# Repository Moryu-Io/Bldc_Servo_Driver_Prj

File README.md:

# BLDC Servo Driver Project

## 概要
STM32マイコンを使用してBLDCを駆動する制御プログラム  
マイコン種類が変わっても、なるべくペリフェラル設定のメンテのみで動作が可能なように実装  
現在のメイン開発は`G431CB_FSDmini`

新ROBO-剣出場ロボット[Quinque](https://www.robo-one.com/rankings/view/1127)のアーム部モータに採用  

## フォルダ構成
| フォルダ名   | 説明                                                                                            |
| ------------ | ----------------------------------------------------------------------------------------------- |
|bldc_servo_driver_mini_F4|STM32F405を使用したBLDCドライバ用コード(未メンテ)|
|bldc_servo_driver_mini_G4|STM32G4系マイコンを使用したBLDCドライバ用コード|
|bldc_servo_driver_mini_H7|STM32H7を使用したBLDCドライバ用コード(未作成)|
|bldc_servo_driver_stspin32g4|STM32G4(STSPIN32G4)を使用したBLDCドライバ用コード|
|common|各マイコンで共通のコード。例えばBLDCベクトル制御ロジック|
|python|各テストコマンドをpython経由で使用するためのスクリプト群|

## 使い方(Windows)
1. 必要Toolのインストール
    - VScode
    - GNU ARM Embedded Toolchain
        - [公式サイト](https://developer.arm.com/tools-and-software/open-source-software/developer-tools/gnu-toolchain/gnu-rm/downloads)
        - Projectとしては2020-q4を使っている。本PJのtask.jsonに記載のディレクトリを変えれば別Verでも使えるはず
        - zip版をDLし, C:\Tools\gcc-arm-none-eabi-9-20XX-qX-major-win32\bin など分かりやすいように配置し、Path を通しておく
    - makeするための何か
        - make for windows, msys2, wslなど。自分は現状msys2でmakeを使えるようにしている
        - 本PJのtask.jsonでは`C:\\msys64\\usr\\bin\\make.exe` がある前提で記載している
    - STM32CubeProgrammer
        - [公式サイト]https://www.st.com/ja/development-tools/stm32cubeprog.html
        - STM32マイコンへのFW書き込みやフラッシュ制御などができる
        - 本PJのtask.jsonではコマンドライン用のexeを利用してマイコンへの書き込みを行っている

2. クローン
    - `git clone https://github.com/Moryu-Io/Bldc_Servo_Driver_Prj.git`など
    - VSCode のタスク構成もついてくるはず

3. VSCode Workspaceを開く
    - 現在は`bldc_servo_driver_G4.code-workspace`推奨

4. Ctrl+Alt+t でタスクを開き`Build project`を実行すると、ビルドができる

5. Ctrl+Alt+t でタスクを開き`cube_program`を実行すると書き込みができる

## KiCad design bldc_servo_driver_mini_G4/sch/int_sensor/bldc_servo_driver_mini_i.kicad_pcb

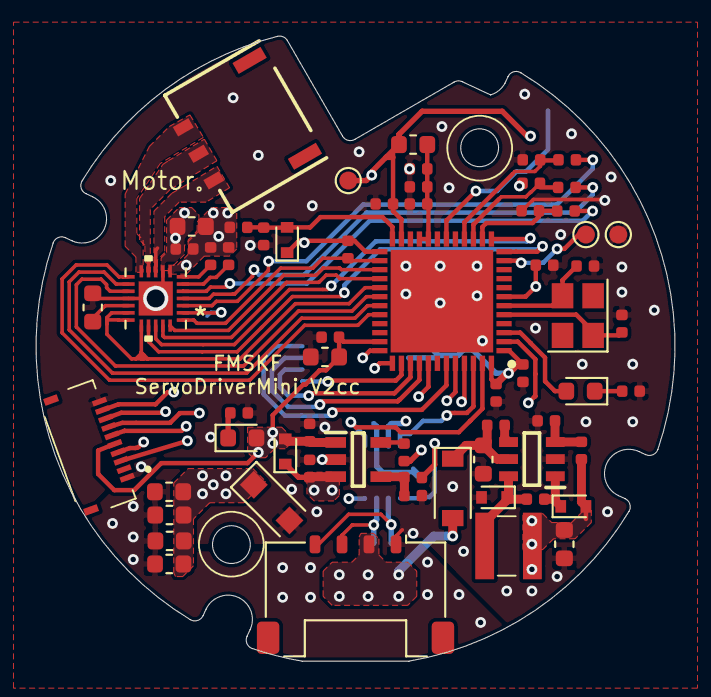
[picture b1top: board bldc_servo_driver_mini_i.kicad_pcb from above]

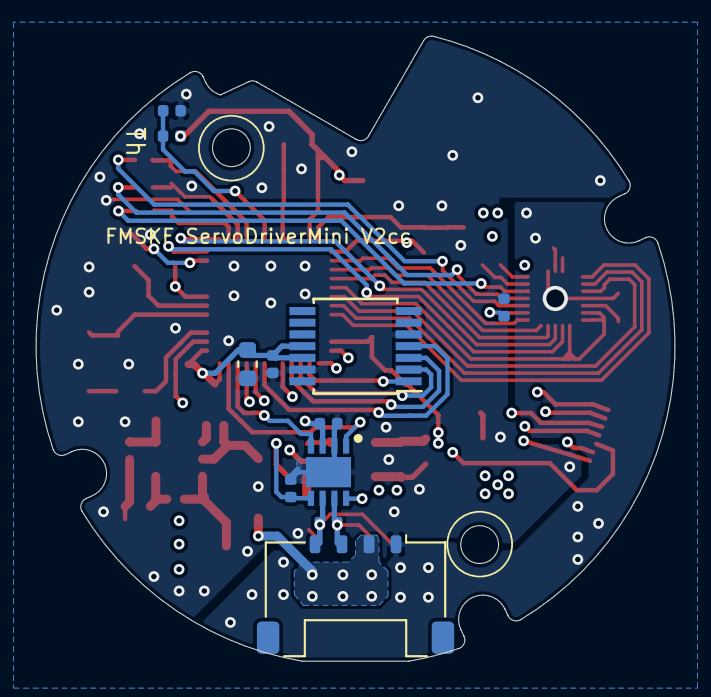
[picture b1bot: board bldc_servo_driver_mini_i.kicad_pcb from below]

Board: 4 copper layers, 35.5 x 34.7 mm, 74 parts (11 on the bottom side), 56 nets.

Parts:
C1, C2, C3, C4, C7, C8, C10, C16, C20, C21, C24, C32: 0.1u; C_0402_1005Metric
C5, C11, C15, C22, C28, C29, C30, C31: 10u; C_0603_1608Metric
C6, C13: 0.01u; C_0402_1005Metric
C9, C14, C23: 1u; C_0402_1005Metric
C12, C25: 4.7u; C_0603_1608Metric
C17, C18, C19: 220pF; C_0402_1005Metric
C26, C27: 8p; C_0402_1005Metric
D1: D_Schottky; D_SOD-123F
D2: PMEG6010AESBYL; D_SOD-123
D3, D4, D9: D_Schottky; D_SOD-523
D5: BAT30KFILM; D_SOD-523
D6, D8: LED; LED_0603_1608Metric
IC1: ST730MR; SOT95P280X145-5N
IC2: LT1616ES6#TRMPBF; SOT95P280X90-6N
IC3: TLT9251VLEXUMA1; SON65P300X300X110-9N
IC4: STM32G4xxyU; QFN50P700X700X60-49N-D
J1: 1-2328702-0; 123287020
J2, J3: Conn_01x04; Molex_Pico-Lock_504050-0491_1x04-1MP_P1.50mm_Horizontal
J7: DF65-3P-1.7V_21_
L1: L; L_0603_1608Metric
L2: 4.7u; LPS3314332MRC
R3, R4, R16, R18, R20: 10k; R_0402_1005Metric
R5: 47k; R_0402_1005Metric
R6: 27k; R_0402_1005Metric
R7: 470k; R_0402_1005Metric
R8: 33k; R_0402_1005Metric
R9, R10, R11: 510; R_0402_1005Metric
R12, R14: 330; R_0402_1005Metric
R15: 60; R_0402_1005Metric
R17: 0; R_0402_1005Metric
R19: 30.1k or 51k(MP2359); R_0402_1005Metric
TH1: Thermistor_NTC; R_0402_1005Metric
TP1, TP2, TP3: TestPoint; TestPoint_Pad_D1.0mm
U1: AS5048A; TSSOP-14_4.4x5mm_P0.65mm
U2: PDRV8311HRRWR
Y1: Crystal; Crystal_SMD_Abracon_ABM8G-4Pin_3.2x2.5mm

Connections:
+3V3: C1.1, C2.1, C5.2, C7.2, C9.1, C10.1, C12.1, C20.1, C21.1, C32.2, D3.2, D5.1, D8.2, IC1.1, IC3.5, IC4.1, IC4.23, IC4.25, IC4.35, IC4.48, J1.5, L1.2, R5.2, R16.1, R18.2, TP1.1, U1.11, U1.12, U2.2
+5V: C8.1, C16.1, C29.2, D3.1, D9.2, IC1.3, IC3.3, L2.2, R4.1, R19.2
+12V: C11.2, C22.1, C23.1, C24.1, C28.2, C30.2, C31.2, D1.1, D2.2, J2.2, J3.2, R7.2, R17.1, U2.8
/CAN1_EN: IC3.8, IC4.2
/CAN1_RX: IC3.4, IC4.46
/CAN1_TX: IC3.1, IC4.47
/CAN_H: IC3.7, J2.3, J3.3, R15.2
/CAN_L: IC3.6, J2.4, J3.4, R15.1
/CurrentSensA: C17.1, IC4.14, R9.1
/CurrentSensB: C18.1, IC4.15, R10.1
/CurrentSensC: C19.1, IC4.16, R11.1
/DAC_O1_GAIN: IC4.12, U2.21
/DAC_O2_SLEW: IC4.13, U2.22
/GPIO_MODE: IC4.28, U2.23
/LED1: D6.2, IC4.3
/M_OUTA: J7.1, U2.10
/M_OUTB: J7.2, U2.11
/M_OUTC: J7.3, U2.12
/NRST: C3.1, IC4.7, J1.4
/Potentio_Sens: IC4.11, TP2.1
/SOA: R9.2, U2.5
/SOB: R10.2, U2.4
/SOC: R11.2, U2.3
/SPI3_CS: IC4.38, U1.1
/SPI3_MISO: IC4.40, U1.3
/SPI3_MOSI: IC4.43, U1.4
/SPI3_SCK: IC4.39, U1.2
/SWCLK: IC4.37, J1.7
/SWDIO: IC4.36, J1.6
/SWO: IC4.41, J1.3
/TIM1_CH1: IC4.30, U2.15
/TIM1_CH1N: IC4.29, U2.18, U2.19, U2.20
/TIM1_CH2: IC4.31, U2.14
/TIM1_CH3: IC4.32, U2.13
/Temp_Sens: IC4.18, R18.1, TH1.1
/USART1_RX: IC4.45, J1.9
/USART1_TX: IC4.44, J1.8
/Vm_Sens: D5.2, IC4.24, R7.1, R8.2
/nFAULT: IC4.26, R16.2, U2.1
/nSLEEP: IC4.27, U2.24
GND: C1.2, C2.2, C3.2, C4.2, C5.1, C7.1, C8.2, C9.2, C10.2, C11.1, C12.2, C13.2, C14.2, C15.1, C16.2, C17.2, C18.2, C19.2, C20.2, C21.2, C22.2, C24.2, C25.1, C26.1, C27.2, C28.1, C29.1, C30.1, C31.1, C32.1, D1.2, D4.2, IC1.2, IC2.2, IC3.2, IC3.9, IC4.49, J1.1, J1.10, J2.1, J3.1, R6.1, R8.1, R12.1, R14.1, R20.1, TH1.2, TP3.1, U1.5, U1.13, U2.9, U2.16, U2.25
unnamed: C6.1, D9.1, IC2.1
unnamed: C6.2, D4.1, IC2.6, L2.1
unnamed: C4.1, C13.1, C14.1, IC4.20, IC4.21, L1.1
unnamed: C15.2, D2.1, IC2.5, R3.2
unnamed: C23.2, U2.6
unnamed: C25.2, U2.17
unnamed: C26.2, IC4.5, Y1.1
unnamed: C27.1, IC4.6, Y1.3
unnamed: D6.1, R12.2
unnamed: D8.1, R14.2
unnamed: IC1.4, R5.1, R6.2
unnamed: IC1.5, R4.2
unnamed: IC2.3, R19.1, R20.2
unnamed: IC2.4, R3.1
unnamed: R17.2, U2.7

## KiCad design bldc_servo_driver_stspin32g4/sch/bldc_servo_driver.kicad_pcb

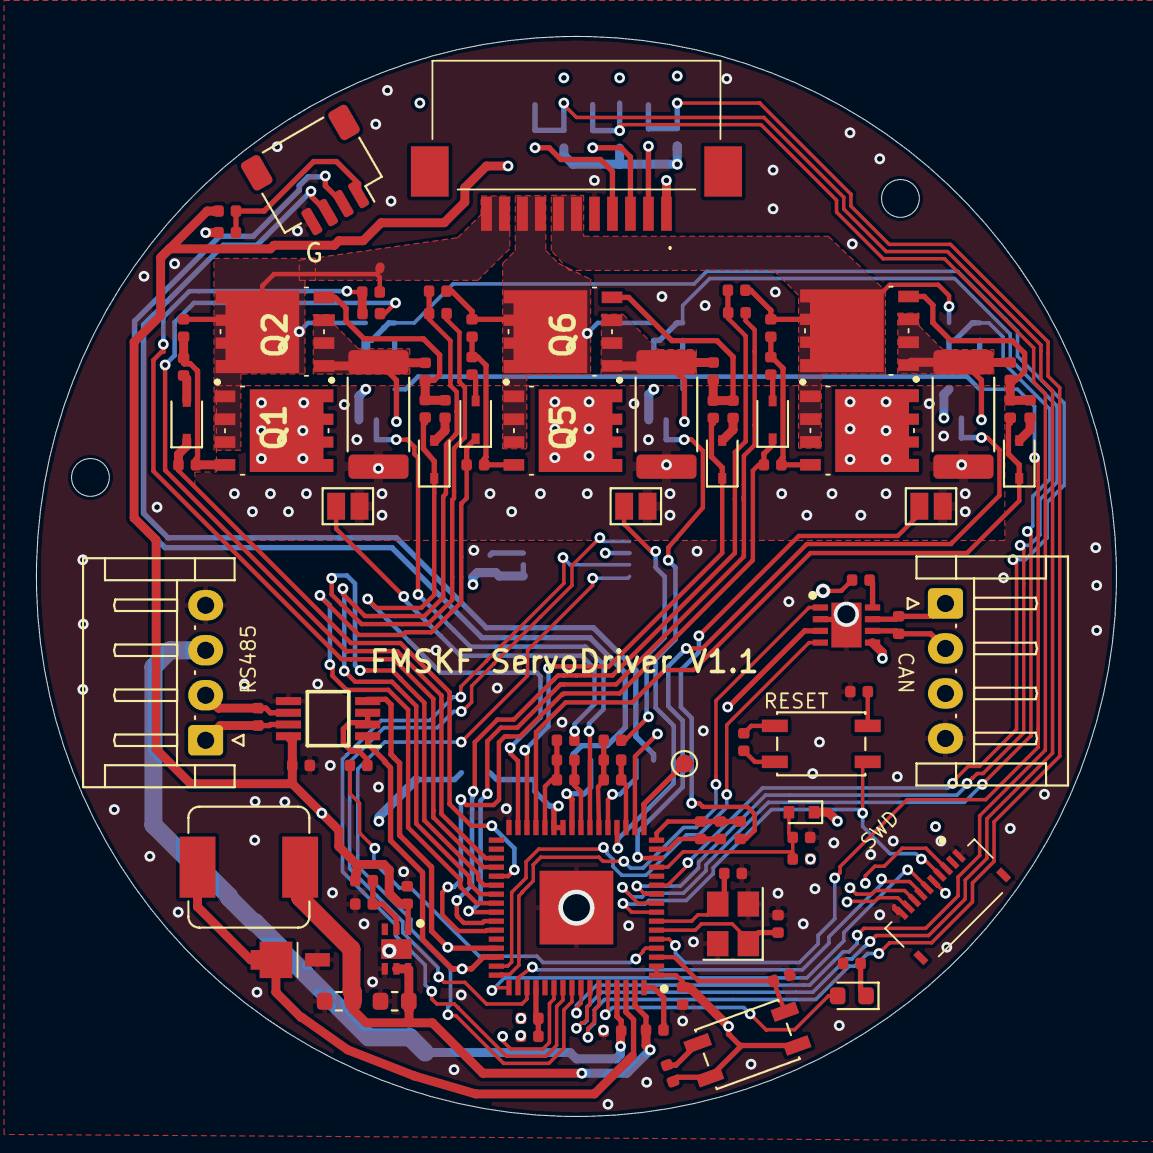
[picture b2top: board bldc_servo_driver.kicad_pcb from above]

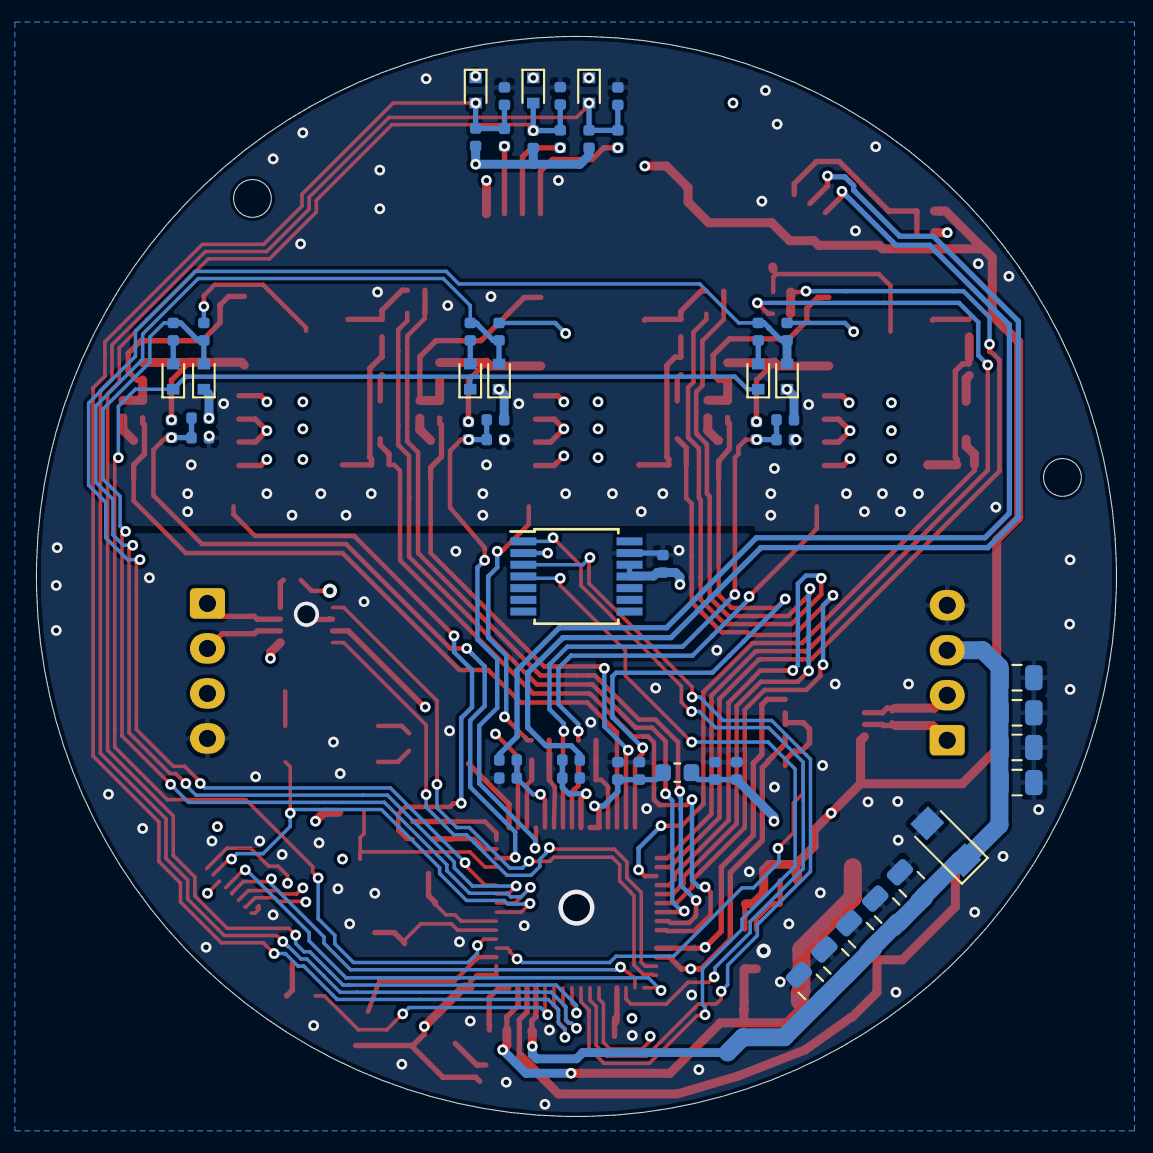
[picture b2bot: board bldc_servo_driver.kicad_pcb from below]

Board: 4 copper layers, 60.0 x 60.0 mm, 150 parts (54 on the bottom side), 97 nets.

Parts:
C1, C2, C3: 10p; C_0402_1005Metric
C4, C8, C20, C25, C50, C52: 0.1u; C_0402_1005Metric
C7: 2.2u; C_0402_1005Metric
C9, C26: 10u; C_0603_1608Metric
C10, C27, C28, C42: 1u; C_0402_1005Metric
C11: 0.01u; C_0402_1005Metric
C12, C14, C15, C17, C19, C29, C30, C31, C32: 22u; C_0805_2012Metric
C13, C16, C22: C; C_0402_1005Metric
C18, C21, C46: 100p; C_0402_1005Metric
C23, C24: 0.001u; C_0402_1005Metric
C53: 4.7u; C_0402_1005Metric
D1, D2, D3, D4, D5, D6, D7, D8, D9, D10: BAT30KFILM; D_SOD-523
D11: SMM4F24A; D_SMF
D12: STPS1L40M
D13: LED; LED_0603_1608Metric
D17, D18, D19, D20, D21, D22: BAT48JFILM; D_SOD-323
H1, H2: MountingHole; MountingHole_2.1mm
IC1: STSPIN32G4; QFN50P900X900X100-65N-D
IC3: LDFMPVR; SON65P200X200X100-7N-D
IC5: SN65HVD485EDGKR; SOP65P490X110-8N
IC6: TLT9251VLEXUMA1; SON65P300X300X110-9N
J1: 1-2328702-0; 123287020
J2, J3: Conn_01x04; JST_EH_S4B-EH_1x04_P2.50mm_Horizontal
J4: 52271-1179; 522711179
J5: Conn_01x04; JST_SH_SM04B-SRSS-TB_1x04-1MP_P1.00mm_Horizontal
JP1, JP2, JP3: SolderJumper_2_Bridged; SolderJumper-2_P1.3mm_Open_Pad1.0x1.5mm
L1: L; L_0603_1608Metric
L2: 33u; L_Sumida_CDMC6D28_7.25x6.5mm
Q1, Q2, Q3, Q4, Q5, Q6: STL180N6F7; STL140N6F7
R1, R5, R7: 1.8k; R_0402_1005Metric
R2, R3, R4, R6, R10, R11, R25, R51, R53, R54, R56, R68, R69, R71: 10k; R_0402_1005Metric
R8: 470k; R_0402_1005Metric
R9: 33k; R_0402_1005Metric
R12, R13, R14: 2.2k; R_0402_1005Metric
R15, R16, R17, R18, R19, R20, R70: 22k; R_0402_1005Metric
R21, R22, R23, R28, R31, R33: 1.5k; R_0402_1005Metric
R24: 52.3k; R_0402_1005Metric
R26, R42: 1k; R_0402_1005Metric
R27, R29, R32: 11k; R_0402_1005Metric
R30, R34, R35, R40, R41, R44, R45, R47, R55, R57, R60, R61, R65, R66: 0; R_0402_1005Metric
R36: 60; R_0402_1005Metric
R37: 120; R_0402_1005Metric
R43: 330; R_0402_1005Metric
R46, R49, R50, R52, R64, R67: 33; R_0402_1005Metric
R48, R58, R59: 0.003; R_2512_6332Metric
R62, R63: 1.6k; R_0402_1005Metric
SW1, SW2: SW_SPST; SW_SPST_EVQP2
TP1: TestPoint; TestPoint_Pad_D1.0mm
U1: AS5048A; TSSOP-14_4.4x5mm_P0.65mm
Y1: ABM8G-25MHZ-18-D2Y-T; Crystal_SMD_Abracon_ABM8G-4Pin_3.2x2.5mm

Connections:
+3.3VA: C10.2, C11.2, IC1.26, IC1.27, L1.2
+3V3: C4.1, C8.1, C50.1, C52.1, C53.1, D1.1, D2.1, D3.1, D4.1, D5.1, D7.1, D8.1, IC1.1, IC1.2, IC6.5, J1.5, L1.1, R6.2, R10.2, R11.2, R15.1, R17.1, R19.1, R41.1, R70.1, SW2.1, U1.11, U1.12
+5V: C7.1, C22.1, IC3.1, IC5.8, IC6.3, J4.1, R24.2, R40.1
+BATT: C12.1, C14.1, C15.1, C17.1, C19.1, C20.1, C29.1, C30.1, C31.1, C32.1, D11.1, IC1.61, J2.3, J3.3, Q1.5, Q1.6, Q1.7, Q1.8, Q1.9, Q3.5, Q3.6, Q3.7, Q3.8, Q3.9, Q5.5, Q5.6, Q5.7, Q5.8, Q5.9, R8.2
/subSch_3phasebridge/BOOT0: C42.1, IC1.41
/subSch_3phasebridge/BOOT1: C28.1, IC1.38
/subSch_3phasebridge/BOOT2: C27.1, IC1.35
/subSch_3phasebridge/GHS0: D19.1, IC1.43, R50.2
/subSch_3phasebridge/GHS1: D20.1, IC1.40, R64.2
/subSch_3phasebridge/GHS2: D17.1, IC1.37, R46.2
/subSch_3phasebridge/GLS0: D21.1, IC1.29, R52.2
/subSch_3phasebridge/GLS1: D22.1, IC1.30, R67.2
/subSch_3phasebridge/GLS2: D18.1, IC1.31, R49.2
/subSch_3phasebridge/MotorD0: J4.6, J4.7, Q3.1, Q3.2, Q3.3, Q4.5, Q4.6, Q4.7, Q4.8, Q4.9, R2.1, R54.2, R55.1
/subSch_3phasebridge/MotorD1: J4.8, J4.9, Q5.1, Q5.2, Q5.3, Q6.5, Q6.6, Q6.7, Q6.8, Q6.9, R3.1, R57.1, R68.2
/subSch_3phasebridge/MotorD2: J4.10, J4.11, Q1.1, Q1.2, Q1.3, Q2.5, Q2.6, Q2.7, Q2.8, Q2.9, R4.1, R44.1, R51.2
/subSch_3phasebridge/VshuntU+: Q4.1, Q4.2, Q4.3, R21.2, R56.2, R58.1
/subSch_3phasebridge/VshuntU-: JP2.2, R28.2
/subSch_3phasebridge/VshuntV+: Q6.1, Q6.2, Q6.3, R22.2, R59.1, R69.2
/subSch_3phasebridge/VshuntV-: JP3.2, R31.2
/subSch_3phasebridge/VshuntW+: Q2.1, Q2.2, Q2.3, R23.2, R48.1, R53.2
/subSch_3phasebridge/VshuntW-: JP1.2, R33.2
/subSch_extcon/ANALOG0: J5.2, R62.1
/subSch_extcon/ANALOG1: J5.3, R63.1
/subSch_extcon/ANALOG2: IC1.17, TP1.1
/subSch_extcon/CAN_EN: IC1.4, R34.1, R35.2
/subSch_extcon/COM_BUS3: IC1.45, IC5.4, J1.8
/subSch_extcon/COM_BUS4: IC1.46, IC5.1, J1.9
/subSch_extcon/Hall_0: J4.3, R1.1
/subSch_extcon/Hall_1: J4.4, R5.1
/subSch_extcon/Hall_2: J4.2, R7.1
/subSch_extcon/USART_EN: IC5.2, IC5.3, R34.2
/subSch_mcu/CAN1_RX: IC1.47, IC6.4
/subSch_mcu/CAN1_TX: IC1.48, IC6.1
/subSch_mcu/HALL_AD_A: C23.1, IC1.25, R62.2
/subSch_mcu/HALL_AD_B: C24.1, IC1.21, R63.2
/subSch_mcu/HALL_U: C1.1, D5.2, IC1.57, R1.2, R6.1
/subSch_mcu/HALL_V: C2.1, D7.2, IC1.58, R5.2, R10.1
/subSch_mcu/HALL_W: C3.1, D8.2, IC1.59, R7.2, R11.1
/subSch_mcu/LED: D13.2, IC1.60
/subSch_mcu/MCU_OUT0: C42.2, IC1.42, R55.2
/subSch_mcu/MCU_OUT1: C28.2, IC1.39, R57.2
/subSch_mcu/MCU_OUT2: C27.2, IC1.36, R44.2
/subSch_mcu/MCU_SPI_BUS0: IC1.56, U1.4
/subSch_mcu/MCU_SPI_BUS1: IC1.55, U1.3
/subSch_mcu/MCU_SPI_BUS2: IC1.18, U1.2
/subSch_mcu/MCU_SPI_BUS3: IC1.51, U1.1
/subSch_mcu/MCU_SWD_BUS0: IC1.50, J1.7
/subSch_mcu/MCU_SWD_BUS1: IC1.49, J1.6
/subSch_mcu/MCU_SWD_BUS2: C25.1, IC1.8, J1.4, SW1.1
/subSch_mcu/MCU_SWD_BUS3: IC1.54, J1.3
/subSch_mcu/MCU_VBAT_MON: D4.2, IC1.13, R8.1, R9.2
/subSch_mcu/OP1M: C46.2, IC1.16, R27.2, R28.1
/subSch_mcu/OP1O: C46.1, IC1.15, R27.1
/subSch_mcu/OP2M: C18.2, IC1.22, R29.2, R31.1
/subSch_mcu/OP2O: C18.1, IC1.19, R29.1
/subSch_mcu/OP3M: C21.2, IC1.28, R32.2, R33.1
/subSch_mcu/OP3O: C21.1, IC1.24, R32.1
/subSch_mcu/SCREF: IC1.52, R70.2, R71.1
/subSch_mcu/SW: D12.1, D12.2, IC1.62, L2.2
/subSch_mcu/USER_SW: C8.2, IC1.3, R26.1, SW2.2
/subSch_onboardsensing/BEMF0: D1.2, IC1.9, R2.2, R12.1
/subSch_onboardsensing/BEMF1: D2.2, IC1.10, R3.2, R13.1
/subSch_onboardsensing/BEMF2: D3.2, IC1.11, R4.2, R14.1
/subSch_onboardsensing/CurFb+_0: IC1.14, R15.2, R16.1, R21.1
/subSch_onboardsensing/CurFb+_1: IC1.20, R17.2, R18.1, R22.1
/subSch_onboardsensing/CurFb+_2: IC1.23, R19.2, R20.1, R23.1
/subSch_onboardsensing/GPIO_BEMF: D6.1, D9.1, D10.1, IC1.5
GND: C1.2, C2.2, C3.2, C4.2, C7.2, C9.2, C10.1, C11.1, C12.2, C13.2, C14.2, C15.2, C16.1, C17.2, C19.2, C20.2, C22.2, C23.2, C24.2, C26.2, C29.2, C30.2, C31.2, C32.2, C50.2, C52.2, C53.2, D11.2, D12.3, IC1.32, IC1.65, IC3.4, IC3.7, IC5.5, IC6.2, IC6.9, J1.1, J1.10, J2.4, J3.4, J4.5, J5.4, JP1.1, JP2.1, JP3.1, R9.1, R16.2, R18.2, R20.2, R25.1, R26.2, R42.2, R43.2, R48.2, R58.2, R59.2, R71.2, U1.13, Y1.2, Y1.4
unnamed: C13.1, IC1.6, Y1.1
unnamed: C16.2, IC1.7, Y1.3
unnamed: C25.2, R42.1, SW1.2
unnamed: D6.2, R12.2
unnamed: D9.2, R13.2
unnamed: D10.2, R14.2
unnamed: D13.1, R43.1
unnamed: D17.2, R45.2
unnamed: D18.2, R47.2
unnamed: D19.2, R60.2
unnamed: D20.2, R61.2
unnamed: D21.2, R65.2
unnamed: D22.2, R66.2
unnamed: IC1.64, R30.2
unnamed: IC3.2, R24.1, R25.2
unnamed: IC5.6, J2.2, R36.2
unnamed: IC5.7, J2.1, R36.1
unnamed: IC6.6, J3.2, R37.1
unnamed: IC6.7, J3.1, R37.2
unnamed: IC6.8, R35.1
unnamed: J5.1, R40.2, R41.2
unnamed: Q1.4, R45.1, R46.1, R51.1
unnamed: Q2.4, R47.1, R49.1, R53.1
unnamed: Q3.4, R50.1, R54.1, R60.1
unnamed: Q4.4, R52.1, R56.1, R65.1
unnamed: Q5.4, R61.1, R64.1, R68.1
unnamed: Q6.4, R66.1, R67.1, R69.1
VCC: C9.1, C26.1, IC1.63, IC3.5, IC3.6, L2.1, R30.1

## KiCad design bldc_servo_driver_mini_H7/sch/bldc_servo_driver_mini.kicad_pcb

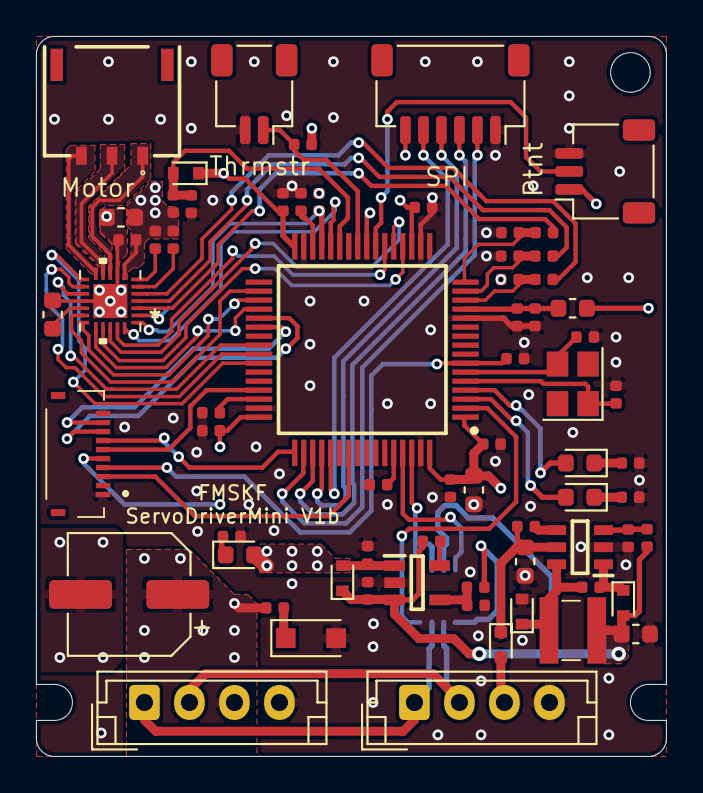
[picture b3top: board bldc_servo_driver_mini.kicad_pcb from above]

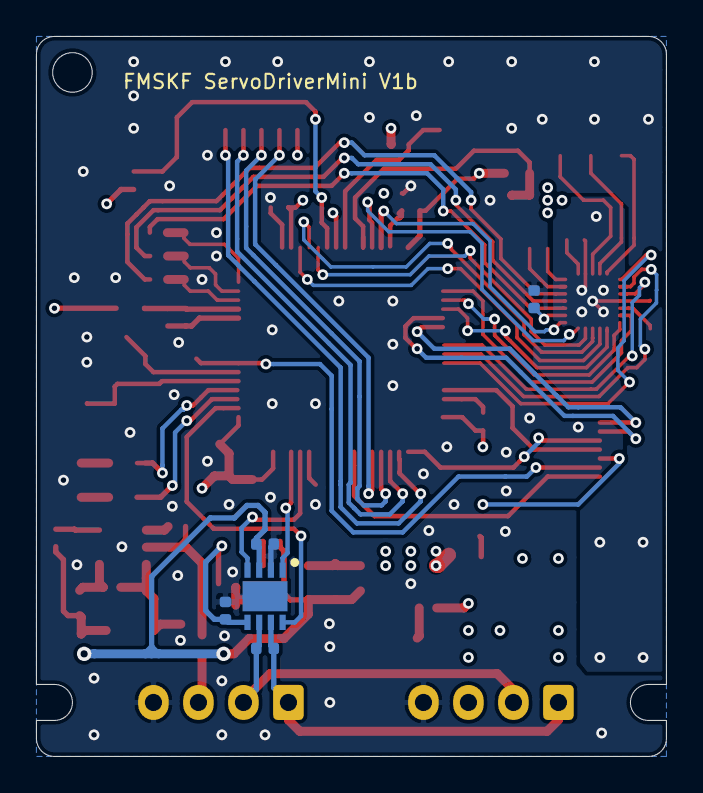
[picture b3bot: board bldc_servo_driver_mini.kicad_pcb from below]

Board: 4 copper layers, 35.0 x 40.0 mm, 73 parts (5 on the bottom side), 64 nets.

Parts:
C1, C3, C4, C7, C8, C10, C11, C13, C16, C20, C21, C24: 0.1u; C_0402_1005Metric
C2, C5: 2.2u; C_0402_1005Metric
C6: 0.01u; C_0402_1005Metric
C9, C14, C23: 1u; C_0402_1005Metric
C12, C25: 4.7u; C_0603_1608Metric
C15, C22, C29: 10u; C_0603_1608Metric
C17, C18, C19: 22pF; C_0402_1005Metric
C26, C27: 8p; C_0402_1005Metric
C28: 47u; CP_Elec_6.3x7.7
D1: D_Schottky; D_SOD-123F
D2: PMEG6010AESBYL; D_SOD-523
D3, D4, D9: D_Schottky; D_SOD-523
D5: BAT30KFILM; D_SOD-523
D6, D7, D8: LED; LED_0603_1608Metric
IC1: ST730MR; SOT95P280X145-5N
IC2: LT1616ES6#TRMPBF; SOT95P280X90-6N
IC3: TLT9251VLEXUMA1; SON65P300X300X110-9N
J1: 1-2328702-0; 123287020
J2, J3: Conn_01x04; JST_EH_B4B-EH-A_1x04_P2.50mm_Vertical
J4: Conn_01x06; JST_SH_SM06B-SRSS-TB_1x06-1MP_P1.00mm_Horizontal
J5: Conn_01x03; JST_SH_SM03B-SRSS-TB_1x03-1MP_P1.00mm_Horizontal
J6: Conn_01x02; JST_SH_SM02B-SRSS-TB_1x02-1MP_P1.00mm_Horizontal
J7: DF65-3P-1.7V_21_
L1: L; L_0603_1608Metric
L2: 4.7u; LPS3314332MRC
R1: 100; R_0402_1005Metric
R2: R; R_0402_1005Metric
R3, R4, R16, R18, R20: 10k; R_0402_1005Metric
R5: 47k; R_0402_1005Metric
R6: 27k; R_0402_1005Metric
R7: 470k; R_0402_1005Metric
R8: 33k; R_0402_1005Metric
R9, R10, R11, R12, R13, R14: 330; R_0402_1005Metric
R15: 60; R_0402_1005Metric
R17: 0; R_0402_1005Metric
R19: 30.1k; R_0402_1005Metric
U1: STM32H7A3RGT6; QFP50P1200X1200X160-64N
U2: PDRV8311HRRWR
Y1: Crystal; Crystal_SMD_Abracon_ABM8G-4Pin_3.2x2.5mm

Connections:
+3V3: C1.1, C4.1, C7.1, C9.1, C10.1, C11.1, C12.1, C20.1, C21.1, D3.2, D5.1, D8.2, IC1.1, IC3.5, J1.5, J4.6, J5.1, L1.2, R5.2, R16.1, R18.2, U1.1, U1.19, U1.24, U1.32, U1.48, U1.64, U2.2
+5V: C8.1, C16.1, C29.2, D3.1, D9.2, IC1.3, IC3.3, L2.2, R4.1, R19.2
+12V: C22.1, C23.1, C24.1, C28.1, D2.2, J2.3, J3.3, R1.2, R7.2, R17.1, U2.8
/CAN1_EN: IC3.8, U1.2
/CAN1_RX: IC3.4, U1.61
/CAN1_TX: IC3.1, U1.62
/CAN_H: IC3.7, J2.1, J3.1, R15.2
/CAN_L: IC3.6, J2.2, J3.2, R15.1
/CurrentSensA: C17.1, R9.1, U1.14
/CurrentSensB: C18.1, R10.1, U1.15
/CurrentSensC: C19.1, R11.1, U1.16
/DAC_O1_GAIN: U1.20, U2.21
/DAC_O2_SLEW: U1.21, U2.22
/GPIO_MODE: U1.22, U2.23
/LED1: D6.2, U1.3
/LED2: D7.2, U1.4
/M_OUTA: J7.1, U2.10
/M_OUTB: J7.2, U2.11
/M_OUTC: J7.3, U2.12
/NRST: C3.1, J1.4, U1.7
/Potentio_Sens: J5.2, U1.23
/SOA: R9.2, U2.5
/SOB: R10.2, U2.4
/SOC: R11.2, U2.3
/SPI3_CS: J4.2, U1.50
/SPI3_MISO: J4.4, U1.52
/SPI3_MOSI: J4.5, U1.53
/SPI3_SCK: J4.3, U1.51
/SWCLK: J1.7, U1.49
/SWDIO: J1.6, U1.45
/SWO: J1.3, U1.55
/TIM1_CH1: U1.40, U2.15
/TIM1_CH1N: U1.34, U2.18
/TIM1_CH2: U1.41, U2.14
/TIM1_CH2N: U1.35, U2.19
/TIM1_CH3: U1.42, U2.13
/TIM1_CH3N: U1.36, U2.20
/Temp_Sens: J6.1, R18.1, U1.25
/USART6_RX: J1.9, U1.38
/USART6_TX: J1.8, U1.37
/Vm_Sens: D5.2, R7.1, R8.2, U1.27
/nFAULT: R16.2, U1.29, U2.1
/nSLEEP: U1.28, U2.24
GND: C1.2, C2.1, C3.2, C4.2, C5.2, C7.2, C8.2, C9.2, C10.2, C11.2, C12.2, C13.2, C14.2, C15.1, C16.2, C17.2, C18.2, C19.2, C20.2, C21.2, C22.2, C24.2, C25.1, C26.1, C27.2, C28.2, C29.1, D1.2, D4.2, IC1.2, IC2.2, IC3.2, IC3.9, J1.1, J1.10, J2.4, J3.4, J4.1, J5.3, J6.2, R2.2, R6.1, R8.1, R12.1, R13.1, R14.1, R20.1, U1.12, U1.18, U1.31, U1.47, U1.63, U2.9, U2.16, U2.25
unnamed: C2.2, U1.30
unnamed: C5.1, U1.46
unnamed: C6.1, D9.1, IC2.1
unnamed: C6.2, D4.1, IC2.6, L2.1
unnamed: C13.1, C14.1, L1.1, U1.13
unnamed: C15.2, D2.1, IC2.5, R3.2
unnamed: C23.2, U2.6
unnamed: C25.2, U2.17
unnamed: C26.2, U1.5, Y1.1
unnamed: C27.1, U1.6, Y1.3
unnamed: D1.1, R1.1
unnamed: D6.1, R12.2
unnamed: D7.1, R13.2
unnamed: D8.1, R14.2
unnamed: IC1.4, R5.1, R6.2
unnamed: IC1.5, R4.2
unnamed: IC2.3, R19.1, R20.2
unnamed: IC2.4, R3.1
unnamed: R2.1, U1.60
unnamed: R17.2, U2.7

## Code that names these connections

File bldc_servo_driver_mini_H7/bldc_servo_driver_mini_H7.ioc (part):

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Mcu.Name=STM32H7A3R(G-I)Tx
Mcu.Package=LQFP64
Mcu.UserName=STM32H7A3RGTx
PA0.Signal=ADC1_INP16
PA1.Mode=IN17-Single-Ended
PA1.Signal=ADC1_INP17
PA10.Signal=S_TIM1_CH3
PA11.Signal=GPIO_Analog
PA13.Signal=DEBUG_JTMS-SWDIO
PA14.Signal=DEBUG_JTCK-SWCLK
PA15.Signal=GPIO_Output
PA2.Signal=ADCx_INP14
PA4.Signal=COMP_DAC11_group
PA5.Signal=COMP_DAC12_group
PA6.Signal=COMP_DAC21_group
PA7.Signal=ADCx_INP7
PA8.Signal=S_TIM1_CH1
PA9.Signal=S_TIM1_CH2
PB0.Signal=S_TIM3_CH3
PB1.Signal=ADCx_INP5
PB10.Signal=GPIO_Input
PB13.Mode=PWM Generation1 CH1 CH1N
PB13.Signal=TIM1_CH1N
PB14.Mode=PWM Generation2 CH2 CH2N
PB14.Signal=TIM1_CH2N
PB15.Mode=PWM Generation3 CH3 CH3N
PB15.Signal=TIM1_CH3N
PB2.Signal=GPIO_Output
PB3.Signal=DEBUG_JTDO-SWO
PB4.Signal=S_TIM3_CH1
PB5.Signal=S_TIM3_CH2
PB6.Signal=USART1_TX
PB7.Signal=USART1_RX
PB8.Mode=FDCAN_Activate
PB8.Signal=FDCAN1_RX
PB9.Mode=FDCAN_Activate
PB9.Signal=FDCAN1_TX
PC10.Signal=SPI3_SCK
PC11.Signal=SPI3_MISO
PC12.Signal=SPI3_MOSI
PC13.Signal=GPIO_Output
PC2.Signal=GPIO_Output
PC3.Signal=GPIO_Output
PC4.Signal=ADCx_INP4
PC5.Signal=ADCx_INP8
PC6.Signal=USART6_TX
PC7.Signal=USART6_RX
PH0-OSC_IN.Mode=HSE-External-Oscillator
PH0-OSC_IN.Signal=RCC_OSC_IN
PH1-OSC_OUT.Mode=HSE-External-Oscillator
PH1-OSC_OUT.Signal=RCC_OSC_OUT
RCC.SYSCLKFreq_VALUE=64000000
board=custom

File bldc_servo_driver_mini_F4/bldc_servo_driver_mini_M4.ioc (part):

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Mcu.Name=STM32F405RGTx
Mcu.Package=LQFP64
Mcu.UserName=STM32F405RGTx
PA0-WKUP.Signal=ADCx_IN0
PA1.Signal=ADCx_IN1
PA10.Signal=S_TIM1_CH3
PA13.Mode=Trace_Asynchronous_SW
PA13.Signal=SYS_JTMS-SWDIO
PA14.Mode=Trace_Asynchronous_SW
PA14.Signal=SYS_JTCK-SWCLK
PA15.GPIOParameters=PinState
PA15.PinState=GPIO_PIN_SET
PA15.Signal=GPIO_Output
PA2.Signal=ADCx_IN2
PA4.Signal=COMP_DAC1_group
PA5.Signal=COMP_DAC2_group
PA6.Signal=GPIO_Output
PA7.Signal=ADCx_IN7
PA8.Signal=S_TIM1_CH1
PA9.Signal=S_TIM1_CH2
PB1.Signal=ADCx_IN9
PB10.Signal=GPIO_Input
PB13.Signal=GPIO_Output
PB14.Signal=GPIO_Analog
PB15.Signal=GPIO_Analog
PB2.Signal=GPIO_Output
PB3.Mode=Trace_Asynchronous_SW
PB3.Signal=SYS_JTDO-SWO
PB8.Mode=CAN_Activate
PB8.Signal=CAN1_RX
PB9.Mode=CAN_Activate
PB9.Signal=CAN1_TX
PC10.Mode=Full_Duplex_Master
PC10.Signal=SPI3_SCK
PC11.Mode=Full_Duplex_Master
PC11.Signal=SPI3_MISO
PC12.Mode=Full_Duplex_Master
PC12.Signal=SPI3_MOSI
PC13-ANTI_TAMP.GPIOParameters=PinState
PC13-ANTI_TAMP.PinState=GPIO_PIN_RESET
PC13-ANTI_TAMP.Signal=GPIO_Output
PC2.Signal=GPIO_Output
PC3.Signal=GPIO_Output
PC4.Signal=ADCx_IN14
PC5.Signal=ADCx_IN15
PC6.Mode=Asynchronous
PC6.Signal=USART6_TX
PC7.Mode=Asynchronous
PC7.Signal=USART6_RX
PH0-OSC_IN.Mode=HSE-External-Oscillator
PH0-OSC_IN.Signal=RCC_OSC_IN
PH1-OSC_OUT.Mode=HSE-External-Oscillator
PH1-OSC_OUT.Signal=RCC_OSC_OUT
RCC.HSE_VALUE=24000000
RCC.SYSCLKFreq_VALUE=168000000
RCC.SYSCLKSource=RCC_SYSCLKSOURCE_PLLCLK
board=custom

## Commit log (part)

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2022-01-08 copy from bldc_servo_driver_cpp repository
2022-01-08 add cubeMX config files of F4 and H7
2022-01-10 style : rename a cubeMx file of H7
2022-01-10 add : kicad projects of driver mini sch
2022-01-10 add : a gitignore file of g4 driver sch
2022-01-10 feat : f4 project
2022-01-10 style :move peripheral driver files
2022-01-10 fix : delete unnecessary include
2022-01-10 feat : [F4]LL library
2022-01-10 feat : [F4] compile ok
2022-01-10 fix : [F4] fix debug lauch file
2022-01-10 feat : [F4] enable debug printf
2022-01-10 style : [F4] rename a CubeMx file
2022-01-12 style : [F4] update vscode config (include path)
2022-01-12 feat : [F4] SPI for a magnet encoder
2022-01-12 feat : [F4] enable timer interrupt for servo and communication control
2022-01-15 feat : [F4] Enable TIM2 for microsec counter
2022-01-15 feat : [F4] BLDC sine drive OK
2022-01-23 feat : [F4] enable ADC tigger
2022-01-23 feat : [F4] spi mode change to 16bit
2022-01-23 fix : [F4sch] generate 5V from DCDC
2022-01-23 feat : [F4] config CAN
2022-02-06 fix : [F4sch] change a diode footprint of 5v line
2022-02-06 fix : [H7sch] apply F4sch update to H7sch
2022-02-06 fix : [G4sch] debug port FPC connector
2022-02-12 style : [F4]arrange cpp wrapper files
2022-02-12 feat : [F4] logger
2022-02-12 fix : [F4] enable printf of float variables
2022-02-12 feat : [F4] 3 phase current sensing
2022-02-12 fix : [Cmn] logger waring
2022-02-12 feat : [F4] enable Vector Control of BLDC
2022-02-12 param : [F4] tuning current pid gain
2022-02-13 feat : [cmn] iir filter
2022-02-13 style : [F4] add python folder path to workspace
2022-02-13 feat : [F4] position servo test
2022-02-13 fix : [cmn] fix double calculating I-Gain of PID
2022-02-13 fix : [F4] fix a angle direction of motor rotor
2022-02-13 feat : [cmn] enable status memories
2022-02-16 param : [F4] tuning
2022-02-16 refactor : [cmn] apply strategy pattern to bldc control class
2022-02-17 refactor : [cmn] bldc class menbers
2022-02-17 feat : [F4] Vmotor sens
2022-02-23 fix : [cmn] fix bug of disable logging
2022-02-23 fix : [cmn] tune controller params
2022-02-23 feat : [cmn] pre-mode
2022-02-23 feat : [F4] current step response test
2022-02-23 style : move a clang-format file
2022-02-23 feat : [F4] enable CAN com
    only test communication
2022-02-26 style : bitfield format
2022-02-26 feat : [F4] CAN com test
2022-02-26 feat : [F4] servo calc time debug
2022-02-26 feat : [cmn] mode status method change
2022-02-26 feat : [F4] torque on off cmd with CAN interface
2022-02-26 feat : [cmn] move angle with CAN
2022-02-27 feat : [F4] Flash
2022-03-12 fix : [F4]bug fix
2022-03-12 feat : [cmn] can simulation by debug uart
2022-03-27 doc : update README
2022-03-27 feat : [F4]elec angle adjust function
2022-03-27 fix : [cmn]current step resp script
2022-03-27 feat : [cmn]flash write test script
2022-05-06 feat : [G4]add a STM32G491 project
2022-05-06 fix : [G4]fix flash pase configs
2022-05-06 feat : [G4] current meas test
2022-05-06 feat : [G4] caribration ADC
2022-05-06 forgot staging file
2022-05-06 fix : [cmn] correct Vm(limit)
2022-05-06 feat : [G4] target setting at first drive
2022-05-06 fix : [G4] CAN filter setting
2022-05-06 fix : [G4] 3D models of sch
2022-05-15 feat : [cmn] pos response test
2022-05-16 feat : [cmn] vector ctrl update (clark conv)
2022-05-16 feat : [G4] pid tune function
2022-05-20 feat : PI-D controller
2022-05-29 feat : initialize a reference angle of pos ctrl
2022-06-01 feat : [cmn] add mode always res summary msg
2022-06-01 feat : [G4] print func of version and build time
2022-06-01 feat : [G4] parameter write func
2022-06-01 [G4] version 01.00
2022-06-11 feat : [python] CAN ID modify script
2022-06-29 feat : current limiter
2022-06-29 [G4] version 01.01
2022-06-29 fix :[G4] CAN config
2022-06-29 feat : false always return res
2022-08-06 [G4] sch update
2022-12-04 feat : params modify script for pm2505
2022-12-04 fix : bldc servo driver mini sch
2022-12-04 refactor : g4 folder struction
2022-12-05 add g431kbESC project
2022-12-12 feat : chip local version
2022-12-25 g431kb_esc setting
2022-12-25 flash modify script for gim4305
2023-01-01 commonalize debug command in progress
2023-01-01 commonalize debug command ( build ok )
2023-01-04 build g431esc
2023-01-04 add g431cb fsdmini project
2023-01-21 refactor current pid gain setting
2023-01-22 gim4305 drive
2023-01-29 feat : current control
2023-02-11 interpolation elec angle
2023-02-11 SPI setting for th modified ESC
2023-02-11 enable spi encoder (G4 ESC)
2023-02-12 [G4ESC] adjust current control parameters
2023-02-23 [g4esc] reduct current meas noises
2023-02-24 [g4esc] CAN trm pin output
2023-03-05 add adustment-test for currents mid
2023-03-05 feat : auto connection for python script
2023-03-05 add manual connection for python script
2023-04-16 [g431] sync timer1 pwm, controller, and adc
2023-04-16 [g431] adjust const variables of control freq
2023-04-20 [G431CBFSD] pwm adc sync
2023-05-04 g4esc model update
2023-05-04 move init cmd update
2023-05-04 g4esc adc trigger timing update
2023-05-05 g431esc : volt step resp test
2023-05-06 debug printf bug fix
2023-05-06 flash read byte command
2023-05-06 g431esc ff kv for current ctrl
2023-05-06 g431esc add res summary2
2023-08-18 [g4cb] maintenance
2023-08-19 g4cb : current lpf
2024-01-03 Common Version 0x0110
2024-01-03 add test cmd of elec angle open drive
2024-01-03 fix python script of flash control
2024-01-03 add test CAN command
2024-01-03 add software spi com
2024-01-03 Common Version 0x0120

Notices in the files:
parts and their libraries:
Copyright 2021 Accelerated Designs. All rights reserved.
